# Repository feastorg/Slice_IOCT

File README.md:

# Slice Template

Rugged digital I/O controller slice with isolated inputs and protected outputs for industrial sensors and actuators.

Template for creating BREAD slices. Features Arduino Nano, small dimensions (70x100mm), 2 layers, and this is the second revision (TEMP_NANO_S2L-r2).

## Introduction

This Slice is designed to be a rugged digital input and output slice that can interface directly with 24V industrial sensors and actuators. It mimics a PLC-style IO module for the BREADS system. It prioritizes input protection, reliable switching, and compatibility with common field devices.

## Usage

[Explain how to use the project. Include examples and screenshots if applicable.]

## Documentation

Please refer to the [docs](/docs) for more info.

---

<div align="center">
  
</div>

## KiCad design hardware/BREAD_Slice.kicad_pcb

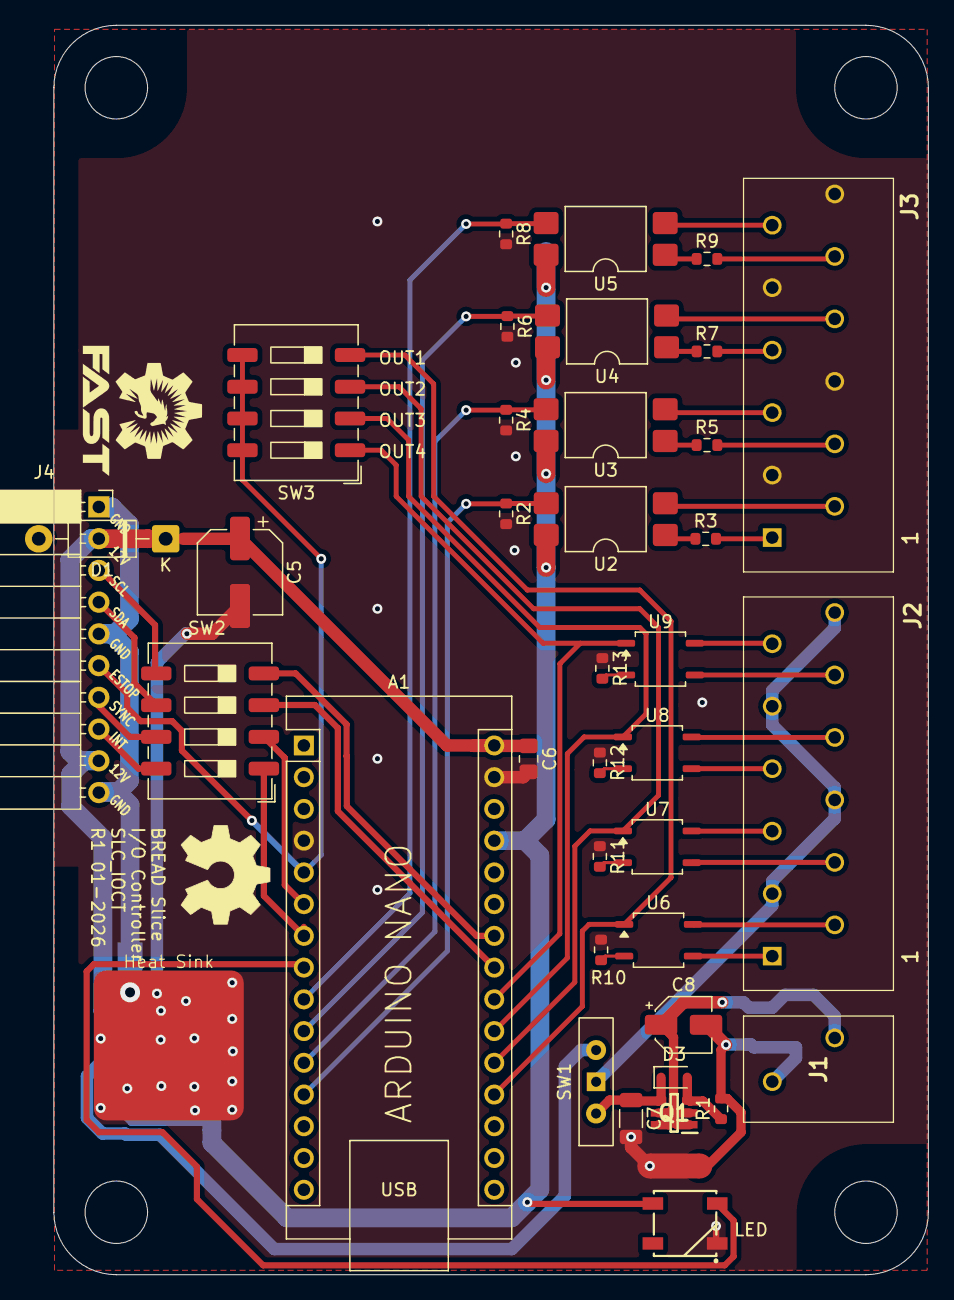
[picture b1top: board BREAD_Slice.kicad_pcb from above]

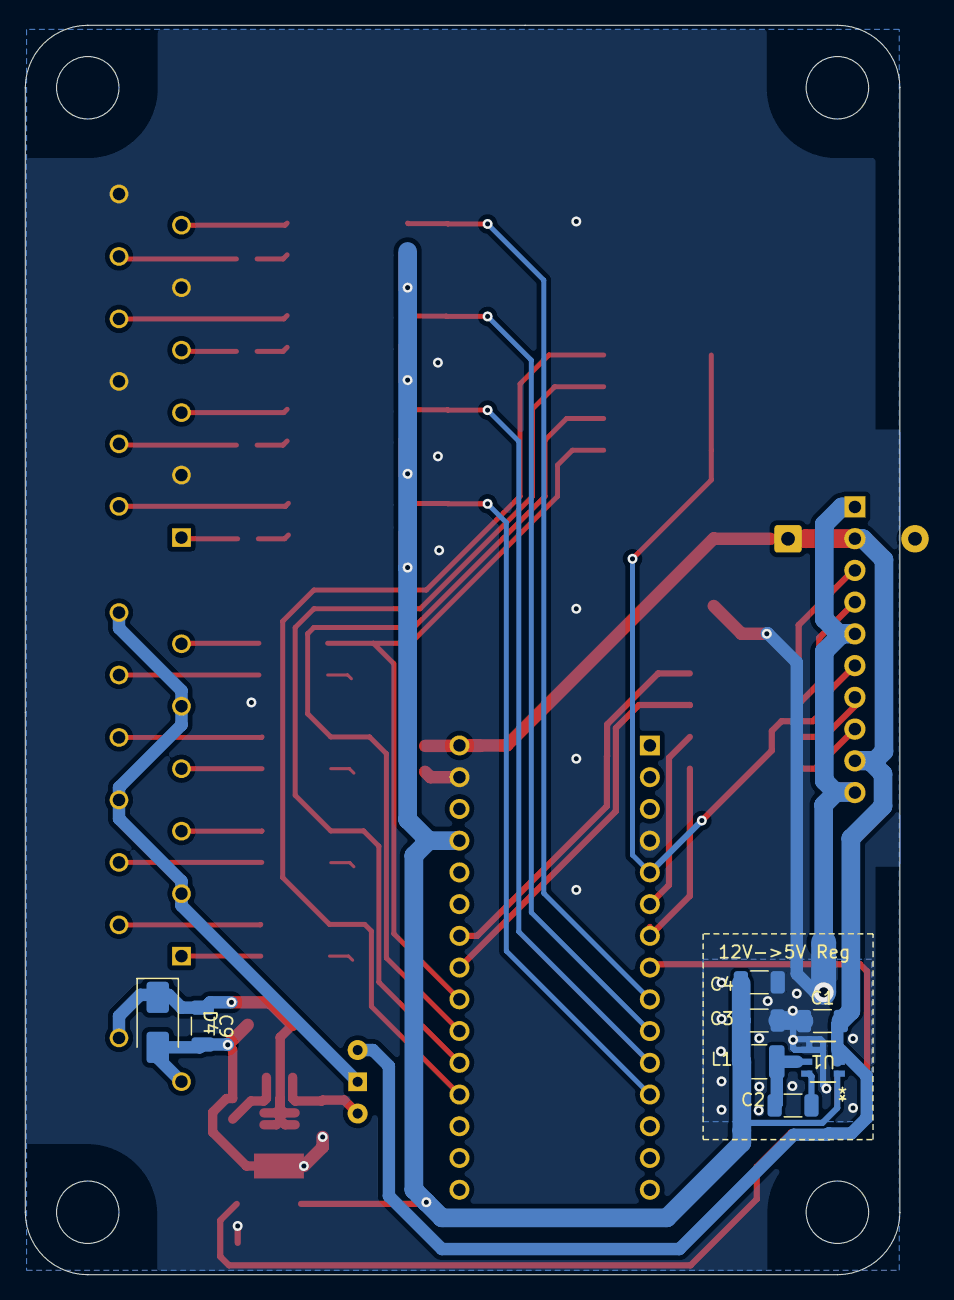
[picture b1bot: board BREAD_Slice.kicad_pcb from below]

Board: 2 copper layers, 70.0 x 100.0 mm, 53 parts (9 on the bottom side), 54 nets.

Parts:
A1: Arduino_Nano_v3.x; Arduino_Nano
C1: 10u; C_1206_3216Metric
C2: 100nF; C_1206_3216Metric
C3, C4: 22uF; C_1206_3216Metric
C5: 47u 25V; CP_Elec_6.3x7.7
C6: 0.1u; C_0805_2012Metric_Pad1.18x1.45mm_HandSolder
C7, C9: 100n; C_1206_3216Metric
C8: 10u; CP_Elec_4x5.8
D1: 1N4007; D_DO-41_SOD81_P10.16mm_Horizontal
D2: WS2812B_5050; WS2812-5050-4PIN
D3: MM3Z18VT1G; D_SOD-323
D4: SMAJ24CA; D_SMA
H1, H2, H3, H4: MountingHole; MountingHole_5mm
HS1: Heatsink_Pad; Thermal_Pad
J1: 1985195
J2, J3: 1990106
J4: Conn_01x10_Socket; PinSocket_1x10_P2.54mm_Horizontal
L1: 4.7uH; L_1210_3225Metric
NT1, NT2: NetTie_2; NetTie-2_SMD_Pad2.0mm
Q1: NTGS4111PT1G; SOT95P275X110-6N
R1: 100k; R_0603_1608Metric
R2, R3, R4, R5, R6, R7, R8, R9: 1k; R_0603_1608Metric
R10, R11, R12, R13: 1.3k; R_0603_1608Metric
Ref**: Val**; OSHW_Logo_8mm
SW1: SW_SPDT; SW_Slide-03_Wuerth-WS-SLTV_10x2.5x6.4_P2.54mm
SW2, SW3: SW_DIP_x04; SW_DIP_SPSTx04_Slide_9.78x12.34mm_W8.61mm_P2.54mm
U1: AP63205; SOIC_05WU-7_DIO
U2, U3, U4, U5: LTV-817S; SMDIP-4_W9.53mm
U6, U7, U8, U9: CPC1002N; SOP-4_3.8x4.1mm_P2.54mm

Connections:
+5V: A1.27 (+5V), C3.2, C4.2, D2.1 (VDD), L1.2, U1.1 (FB), U2.4, U3.4, U4.4, U5.4
+12V: C1.2, D1.2 (A), J4.2, J4.9, SW1.1 (A), U1.2 (EN), U1.3 (VIN)
/+24V: C7.1, D3.1 (K), Q1.4 (S), SW1.3 (C)
/ESTOP: A1.5 (D2), J4.6, SW3.5, SW3.6, SW3.7, SW3.8
/I2C_CLK: A1.24 (A5), SW2.4
/I2C_DAT: A1.23 (A4), SW2.3
/IN1: A1.12 (D9), R2.1, U2.3
/IN1+: J3.1, R3.2
/IN1-: J3.2, U2.2
/IN2: A1.11 (D8), R4.1, U3.3
/IN2+: J3.4, R5.2
/IN2-: J3.5, U3.2
/IN3: A1.10 (D7), R6.1, U4.3
/IN3+: J3.7, R7.2
/IN3-: J3.8, U4.2
/IN4: A1.9 (D6), R8.1, U5.3
/IN4+: J3.10, R9.2
/IN4-: J3.11, U5.2
/Input Power Protection/INPUT_GND: C8.2, C9.2, D4.2 (A2), J1.2, NT2.2, R1.2
/Input Power Protection/INPUT_VDD: C8.1, C9.1, D4.1 (A1), J1.1, Q1.1 (D_1), Q1.2 (D_2), Q1.5 (D_3), Q1.6 (D_4)
/OUT1: A1.19 (A0), SW3.4, U6.1
/OUT1+: J2.2, U6.4
/OUT1-: J2.1, U6.3
/OUT2: A1.20 (A1), SW3.3, U7.1
/OUT2+: J2.4, U7.3
/OUT2-: J2.5, U7.4
/OUT3: A1.21 (A2), SW3.2, U8.1
/OUT3+: J2.7, U8.3
/OUT3-: J2.8, U8.4
/OUT4: A1.22 (A3), SW3.1, U9.1
/OUT4+: J2.10, U9.3
/OUT4-: J2.11, U9.4
/VFIELD: J2.3, J2.6, J2.9, J2.12, SW1.2 (B)
/slice_template/I2C_CLK: J4.3, SW2.5
/slice_template/I2C_DAT: J4.4, SW2.6
/slice_template/INT: J4.8, SW2.8
/slice_template/INT/CAN_{CS}: A1.7 (D4), SW2.1
/slice_template/LED: A1.8 (D5), D2.4 (DIN)
/slice_template/SYNC: J4.7, SW2.7
/slice_template/SYNC/CAN_{INT}: A1.6 (D3), SW2.2
/slice_template/VIN: A1.30 (VIN), C5.1, C6.1, D1.1 (K)
GND: A1.4 (GND), A1.29 (GND), C1.1, C3.1, C4.1, C5.2, C6.2, C7.2, D2.3 (VSS), HS1.1, J3.3, J3.6, J3.9, J3.12, NT1.1, NT2.1, R2.2, R4.2, R6.2, R8.2, R10.1, R11.1, R12.1, R13.1, U1.4 (GND)
GNDPWR: J4.1, J4.5, J4.10, NT1.2
unnamed: D3.2 (A), Q1.3 (G), R1.1
unnamed: R3.1, U2.1
unnamed: R5.1, U3.1
unnamed: R7.1, U4.1
unnamed: R9.1, U5.1
unnamed: R10.2, U6.2
unnamed: R11.2, U7.2
unnamed: R12.2, U8.2
unnamed: R13.2, U9.2
unnamed: C2.2, U1.6 (BST)
unnamed: C2.1, L1.1, U1.5 (SW)

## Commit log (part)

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2025-09-28 📄 KiBot index + board renders (auto)
2025-09-28 add plan doc and disable actions for now
2025-11-11 Finished draft 1, still need documentation and review
2025-11-11 remove planning doc move to arch for dispersal later
2025-11-11 remove obsidian metadata
2025-11-11 add obsidian to gitignore
2025-11-11 some revisions and schem and brd
2025-11-11 remove dsstore
2025-11-11 further revision of schem, add subsheets
2025-11-11 add parts list of some terminal options
2025-11-11 update schem
2025-11-12 finalize revision of schematic
2025-11-12 add some more notes to components listing so i can close my tabs out
2025-12-27 Added new conenctor
2025-12-27 updated routing and silkscreen
2026-01-02 go over changes with ian, fix courtyard outline
2026-01-03 fix some footprint links
2026-01-03 remove duplicate in gitignore
2026-01-04 revision of symbol attachment and clear out old layout and start new; kml-custom to kmlib-local
2026-01-05 rerouted using PTSA connectors
2026-01-11 rerouted again with new kml library
2026-02-09 update all to KMLib, untrack backups in gitignore, and revise routing on board to simplify
2026-03-25 added to todo
2026-04-20 refactor: org casing rename from 'FEASTorg' to 'feastorg'
2026-05-20 Add slice.yaml manifest (schema v1.0)
2026-05-22 added dip switches to IOCT
2026-05-22 updated todo
2026-05-24 Add TODO.md with pipeline status
2026-05-24 chore: desc. to readme
2026-05-24 Standardize TODO.md with Pass 1/Pass 2 structure
2026-05-29 added silkscreen for dip switches
